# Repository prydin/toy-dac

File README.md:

# toy-dac

A 1-bit ΔΣ stereo audio DAC implemented on a Xilinx 7-series FPGA
(Digilent Cmod S7), driven from an I²S input.

The signal chain is entirely homemade RTL:

- **I²S receiver** with double-flopped synchronizers and AXI-Stream output
- **Automatic input rate detection** (32 / 44.1 / 48 kHz)
- **Fractional-phase polyphase ASRC** — 256 phases × 64 taps × 18-bit
  coefficients with 16-bit alpha lerp, single time-shared MAC, PI servo
  on the input ring-buffer fill — resampling onto a fixed
  Fs<sub>out</sub> = MCLK / 64 = 1.6875 MHz output grid
- **2nd-order CIFB ΔΣ modulator** (per channel) with TPDF dither,
  driving a single-bit differential output pin pair on each channel
- A small reconstruction filter and analog output stage on the carrier PCB

Internal test sources (silent, DC, 1 kHz DDS sine) and a bypass mode
(raw I²S → modulator) are included for bring-up and characterisation.

Achieved performance with the current build is roughly 70 dB SNR and
−74 dB THD at −7 dBFS, 1 kHz; harmonic distortion is dominated by the
analog stage on the prototype board.

## Status

**Experimental.** This is a personal learning / hobby project. The
design works end-to-end on the target hardware, but it has had limited
testing, no formal verification, and the analog board is a hand-routed
prototype. Module ports, parameter names, and pinouts may change without
notice. Use it for inspiration or as a starting point, not as a drop-in
IP.

## Repository layout

```
fpga/toy-dac/   Vivado project (RTL under src/rtl, constraints under
                toy-dac.srcs/constrs_1, simulation under toy-dac.srcs/sim_1)
kicad/dac/      KiCad schematic + PCB for the analog carrier board
scripts/        Coefficient generation, simulation helpers, sanity checks
docs/           Block diagrams (top-level + ASRC internals)
```

## Building

Open `fpga/toy-dac/toy-dac.xpr` in Vivado 2024.2, run synthesis +
implementation + bitstream generation, and program the Cmod S7. The
target part and pin assignments live in
`fpga/toy-dac/toy-dac.srcs/constrs_1/new/root.xdc`.

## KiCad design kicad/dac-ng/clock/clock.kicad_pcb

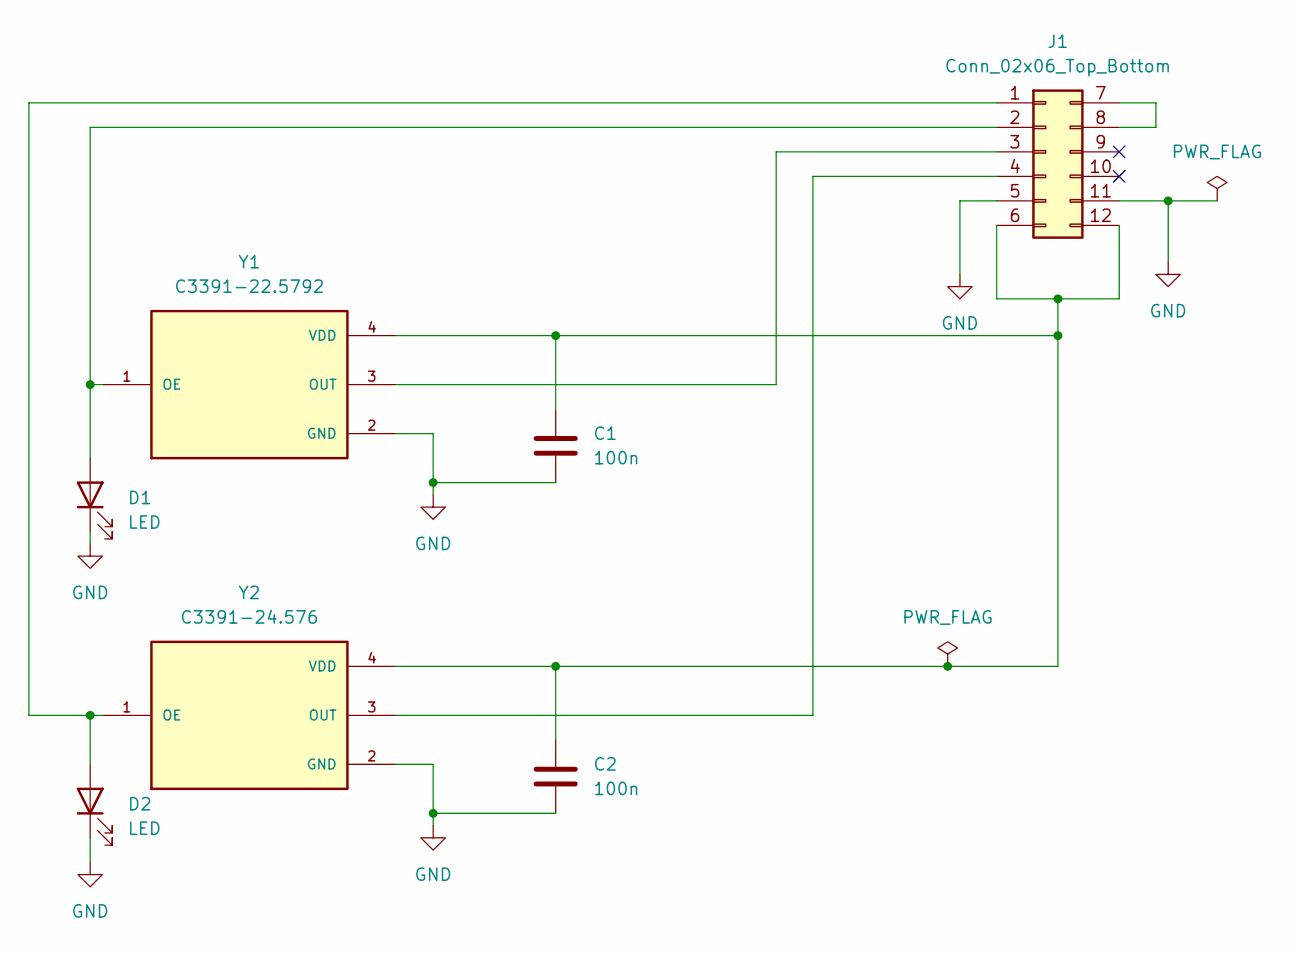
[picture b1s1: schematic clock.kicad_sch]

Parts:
C1, C2: 100n; C_0603_1608Metric_Pad1.08x0.95mm_HandSolder
D1, D2: LED; LED_0603_1608Metric
J1: Conn_02x06_Top_Bottom; PinHeader_2x06_P2.54mm_Vertical
Y1: C3391-22.5792; Oscillator_SMD_Diodes_FN-4Pin_7.0x5.0mm; PARTREV NA
Y2: C3391-24.576; Oscillator_SMD_Diodes_FN-4Pin_7.0x5.0mm; PARTREV NA

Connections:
GND: C1.2, C2.2, D1.1 (K), D2.1 (K), J1.5, J1.11, Y1.2 (GND), Y2.2 (GND)
unnamed: D1.2 (A), J1.2, Y1.1 (OE)
unnamed: D2.2 (A), J1.1, Y2.1 (OE)
unnamed: J1.3, Y1.3 (OUT)
unnamed: J1.4, Y2.3 (OUT)
unnamed: J1.7, J1.8
unnamed: C1.1, C2.1, J1.6, J1.12, Y1.4 (VDD), Y2.4 (VDD)

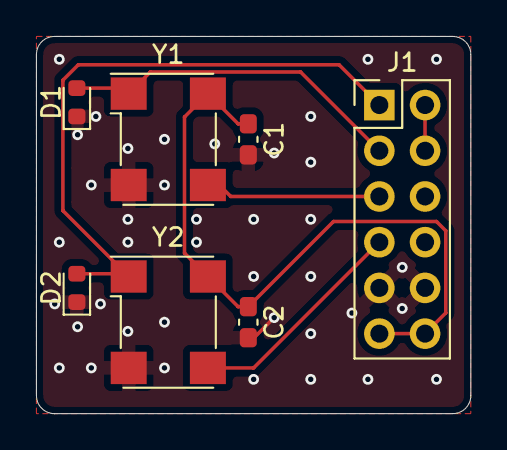
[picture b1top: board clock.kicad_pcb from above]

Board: 2 copper layers, 24.1 x 21.0 mm, 7 parts (0 on the bottom side), 7 nets.

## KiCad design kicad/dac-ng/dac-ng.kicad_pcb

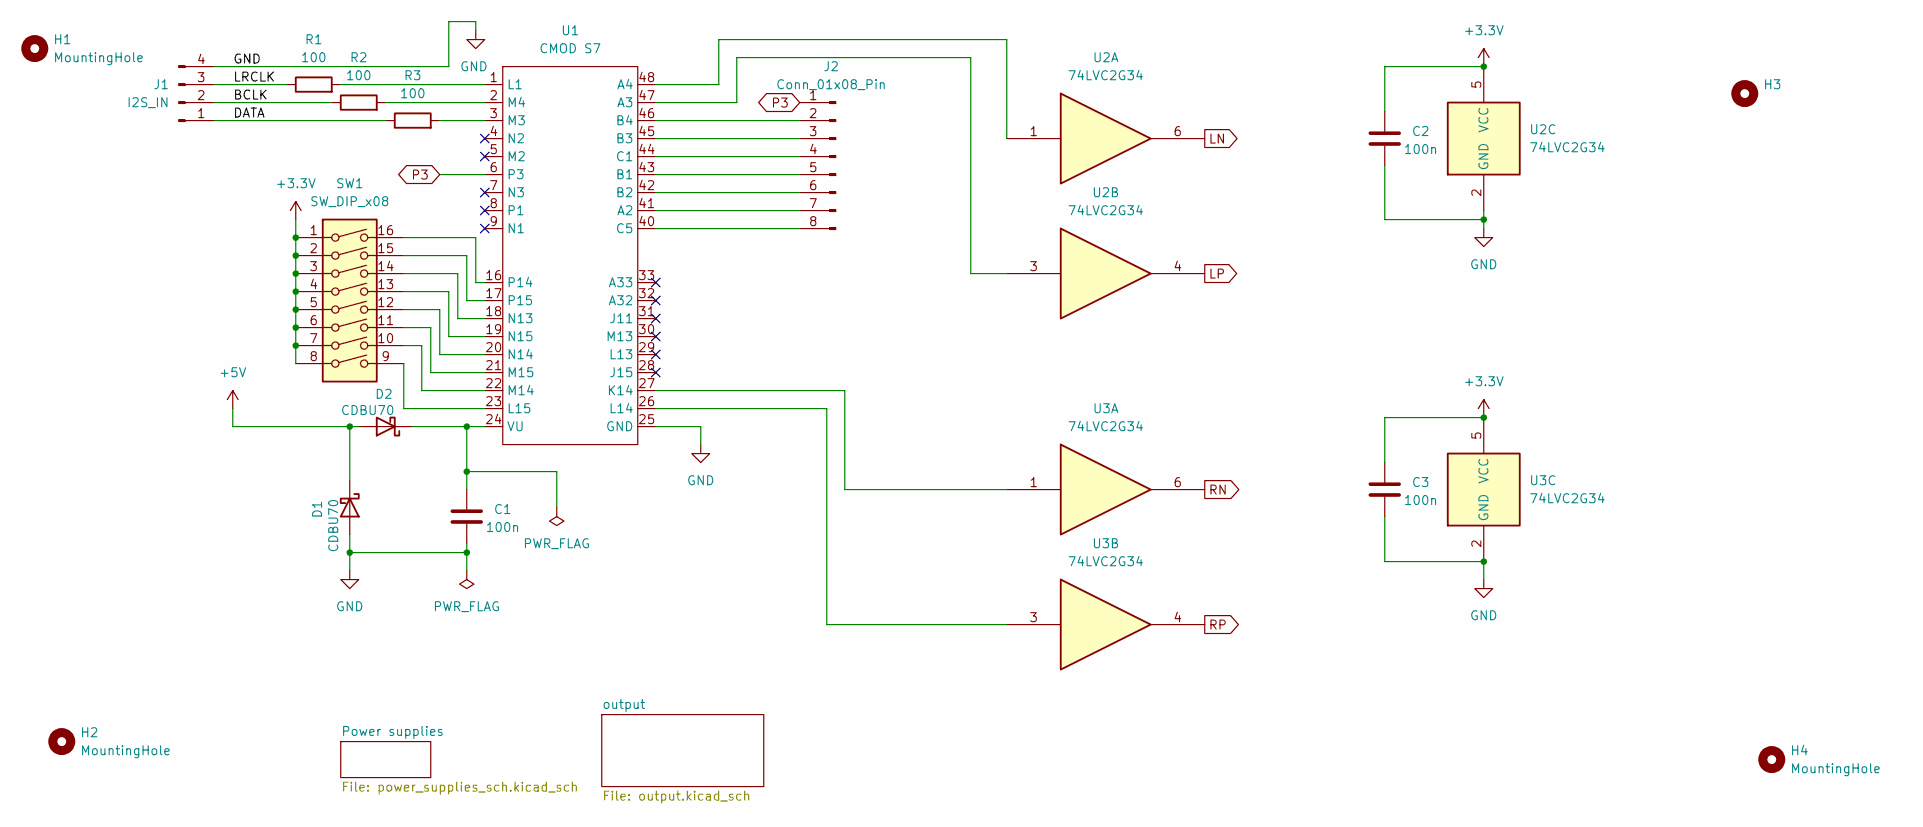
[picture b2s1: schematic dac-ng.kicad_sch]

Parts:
C1, C2, C3: 100n; C_0603_1608Metric_Pad1.08x0.95mm_HandSolder
D1, D2: CDBU70; D_0603_1608Metric
H1, H2, H3, H4: MountingHole; MountingHole_3.2mm_M3
J1: I2S_IN; JST_PH_B4B-PH-K_1x04_P2.00mm_Vertical
J2: Conn_01x08_Pin; PinHeader_1x08_P2.54mm_Vertical
R1, R2, R3: 100; R_0603_1608Metric_Pad0.98x0.95mm_HandSolder
SW1: SW_DIP_x08; SW_DIP_SPSTx08_Slide_6.7x21.88mm_W7.62mm_P2.54mm_LowProfile
U1: CMOD S7
U2, U3: 74LVC2G34; SOT-363_SC-70-6

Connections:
+3.3V: C2.2, C3.2, SW1.1, SW1.2, SW1.3, SW1.4, SW1.5, SW1.6, SW1.7, SW1.8, U2.5 (VCC), U3.5 (VCC); also elsewhere on the board
+5V: D1.1 (K), D2.2 (A); also elsewhere on the board
/BCLK: J1.2, R2.1
/DATA: J1.1, R3.1
/LRCLK: J1.3, R1.1
GND: C1.1, C2.1, C3.1, D1.2 (A), J1.4, U1.25 (GND), U2.2 (GND), U3.2 (GND); also elsewhere on the board
LN: U2.6; also elsewhere on the board
LP: U2.4; also elsewhere on the board
unnamed: C1.2, D2.1 (K), U1.24 (VU)
unnamed: J2.2, U1.46 (B4)
unnamed: J2.3, U1.45 (B3)
unnamed: J2.4, U1.44 (C1)
unnamed: J2.5, U1.43 (B1)
unnamed: J2.6, U1.42 (B2)
unnamed: J2.7, U1.41 (A2)
unnamed: J2.8, U1.40 (C5)
unnamed: U1.47 (A3), U2.3
unnamed: U1.48 (A4), U2.1
unnamed: U1.27 (K14), U3.1
unnamed: R1.2, U1.1 (L1)
unnamed: U1.26 (L14), U3.3
unnamed: SW1.9, U1.23 (L15)
unnamed: R3.2, U1.3 (M3)
unnamed: R2.2, U1.2 (M4)
unnamed: SW1.10, U1.22 (M14)
unnamed: SW1.11, U1.21 (M15)
unnamed: SW1.14, U1.18 (N13)
unnamed: SW1.12, U1.20 (N14)
unnamed: SW1.13, U1.19 (N15)
unnamed: SW1.16, U1.16 (P14)
unnamed: SW1.15, U1.17 (P15)
P3: J2.1, U1.6 (P3)
RN: U3.6; also elsewhere on the board
RP: U3.4; also elsewhere on the board

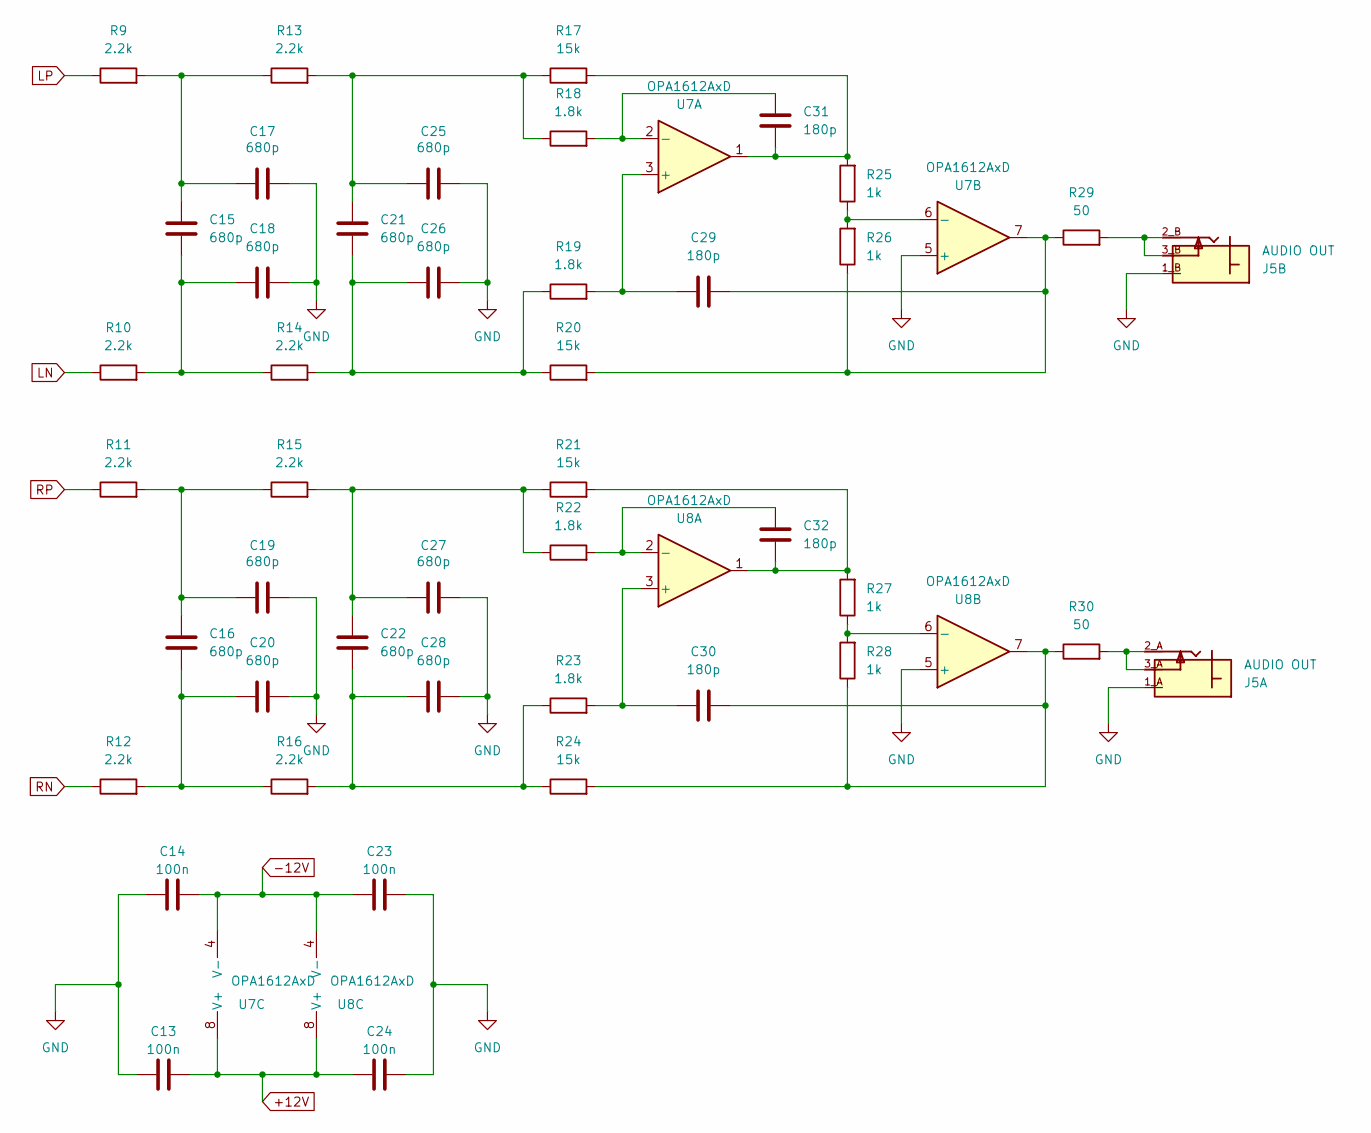
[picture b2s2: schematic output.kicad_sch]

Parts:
C13, C14, C23, C24: 100n; C_0603_1608Metric_Pad1.08x0.95mm_HandSolder
C15, C16, C17, C18, C19, C20, C21, C22, C25, C26, C27, C28: 680p; C_0603_1608Metric_Pad1.08x0.95mm_HandSolder
C29, C30, C31, C32: 180p; C_0603_1608Metric_Pad1.08x0.95mm_HandSolder
J5: AUDIO OUT; SWITCHCRAFT_PJRAN2X1U01AUX
R9, R10, R11, R12, R13, R14, R15, R16: 2.2k; R_0603_1608Metric_Pad0.98x0.95mm_HandSolder
R17, R20, R21, R24: 15k; R_0603_1608Metric_Pad0.98x0.95mm_HandSolder
R18, R19, R22, R23: 1.8k; R_0603_1608Metric_Pad0.98x0.95mm_HandSolder
R25, R26, R27, R28: 1k; R_0603_1608Metric_Pad0.98x0.95mm_HandSolder
R29, R30: 50; R_0603_1608Metric_Pad0.98x0.95mm_HandSolder
U7, U8: OPA1612AxD; SOIC-8_5.3x5.3mm_P1.27mm

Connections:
+12V: C13.2, C24.2, U7.8 (V+), U8.8 (V+); also elsewhere on the board
-12V: C14.2, C23.2, U7.4 (V-), U8.4 (V-); also elsewhere on the board
GND: C13.1, C14.1, C17.2, C18.2, C19.2, C20.2, C23.1, C24.1, C25.2, C26.2, C27.2, C28.2, J5.1_A, J5.1_B, U7.5 (+), U8.5 (+); also elsewhere on the board
LN: R10.1; also elsewhere on the board
LP: R9.1; also elsewhere on the board
unnamed: C15.1, C17.1, R9.2, R13.1
unnamed: C15.2, C18.1, R10.2, R14.1
unnamed: C16.1, C19.1, R11.2, R15.1
unnamed: C16.2, C20.1, R12.2, R16.1
unnamed: C21.1, C25.1, R13.2, R17.1, R18.1
unnamed: C21.2, C26.1, R14.2, R19.1, R20.1
unnamed: C22.1, C27.1, R15.2, R21.1, R22.1
unnamed: C22.2, C28.1, R16.2, R23.1, R24.1
unnamed: C29.2, R20.2, R26.1, R29.1, U7.7
unnamed: C30.2, R24.2, R28.1, R30.1, U8.7
unnamed: C31.2, R17.2, R25.2, U7.1
unnamed: C32.2, R21.2, R27.2, U8.1
unnamed: J5.2_A, J5.3_A, R30.2
unnamed: J5.2_B, J5.3_B, R29.2
unnamed: C29.1, R19.2, U7.3 (+)
unnamed: C31.1, R18.2, U7.2 (-)
unnamed: R25.1, R26.2, U7.6 (-)
unnamed: C30.1, R23.2, U8.3 (+)
unnamed: C32.1, R22.2, U8.2 (-)
unnamed: R27.1, R28.2, U8.6 (-)
RN: R12.1; also elsewhere on the board
RP: R11.1; also elsewhere on the board

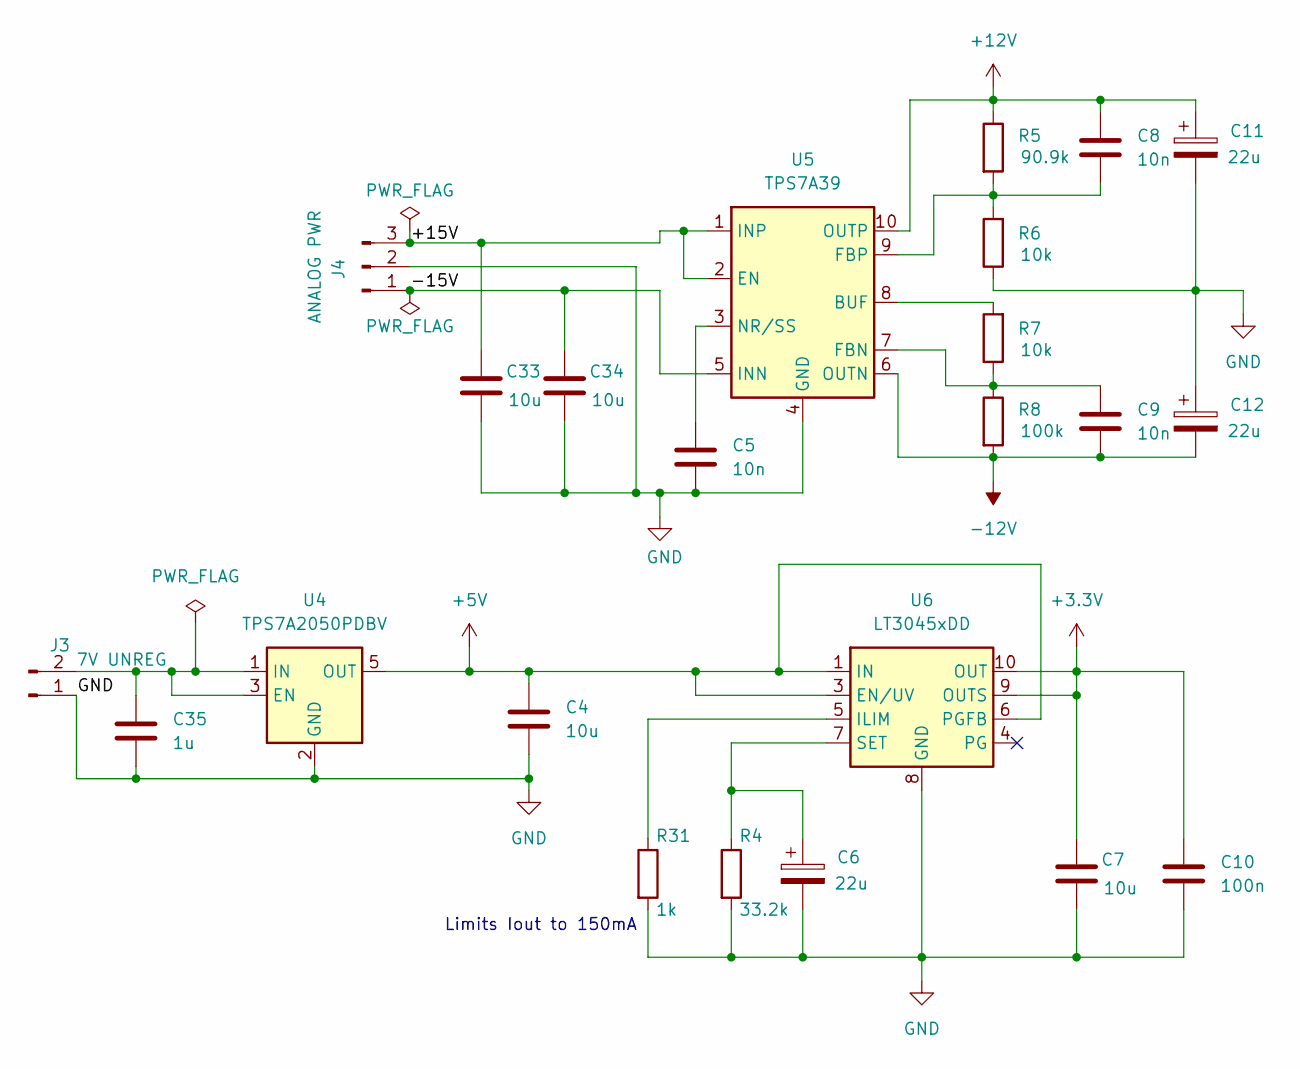
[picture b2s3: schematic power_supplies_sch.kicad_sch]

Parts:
C4, C7, C33, C34: 10u; C_0805_2012Metric
C5, C8, C9: 10n; C_0603_1608Metric_Pad1.08x0.95mm_HandSolder
C6, C11, C12: 22u; CP_EIA-3216-10_Kemet-I_HandSolder
C10: 100n; C_0603_1608Metric_Pad1.08x0.95mm_HandSolder
C35: 1u; C_0603_1608Metric
J3: 7V UNREG; JST_PH_B2B-PH-K_1x02_P2.00mm_Vertical
J4: ANALOG PWR; JST_PH_B3B-PH-K_1x03_P2.00mm_Vertical
R4: 33.2k; R_0603_1608Metric_Pad0.98x0.95mm_HandSolder
R5: 90.9k; R_0603_1608Metric_Pad0.98x0.95mm_HandSolder
R6, R7: 10k; R_0603_1608Metric_Pad0.98x0.95mm_HandSolder
R8: 100k; R_0603_1608Metric_Pad0.98x0.95mm_HandSolder
R31: 1k; R_0603_1608Metric_Pad0.98x0.95mm_HandSolder
U4: TPS7A2050PDBV; SOT-23-5
U5: TPS7A39; Texas_S-PVSON-N10_ThermalVias
U6: LT3045xDD; DFN-10-1EP_3x3mm_P0.5mm_EP1.65x2.38mm

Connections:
+3.3V: C7.1, C10.1, U6.9 (OUTS), U6.10 (OUT); also elsewhere on the board
+5V: C4.1, U4.5 (OUT), U6.1 (IN), U6.2 (IN), U6.3 (EN/UV), U6.6 (PGFB); also elsewhere on the board
+12V: C8.1, C11.1, R5.1, U5.10 (OUTP); also elsewhere on the board
-12V: C9.2, C12.2, R8.2, U5.6 (OUTN); also elsewhere on the board
/Power supplies/+15V: C33.1, J4.3, U5.1 (INP), U5.2 (EN)
/Power supplies/-15V: C34.1, J4.1, U5.5 (INN)
GND: C4.2, C5.2, C6.2, C7.2, C10.2, C11.2, C12.1, C33.2, C34.2, C35.2, J3.1, J4.2, R4.2, R6.1, R31.2, U4.2 (GND), U5.4 (GND), U5.11 (GND), U6.8 (GND), U6.11 (GND); also elsewhere on the board
unnamed: C35.1, J3.2, U4.1 (IN), U4.3 (EN)
unnamed: R7.2, U5.8 (BUF)
unnamed: C9.1, R7.1, R8.1, U5.7 (FBN)
unnamed: C8.2, R5.2, R6.2, U5.9 (FBP)
unnamed: C5.1, U5.3 (NR/SS)
unnamed: R31.1, U6.5 (ILIM)
unnamed: C6.1, R4.1, U6.7 (SET)

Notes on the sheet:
Limits Iout to 150mA

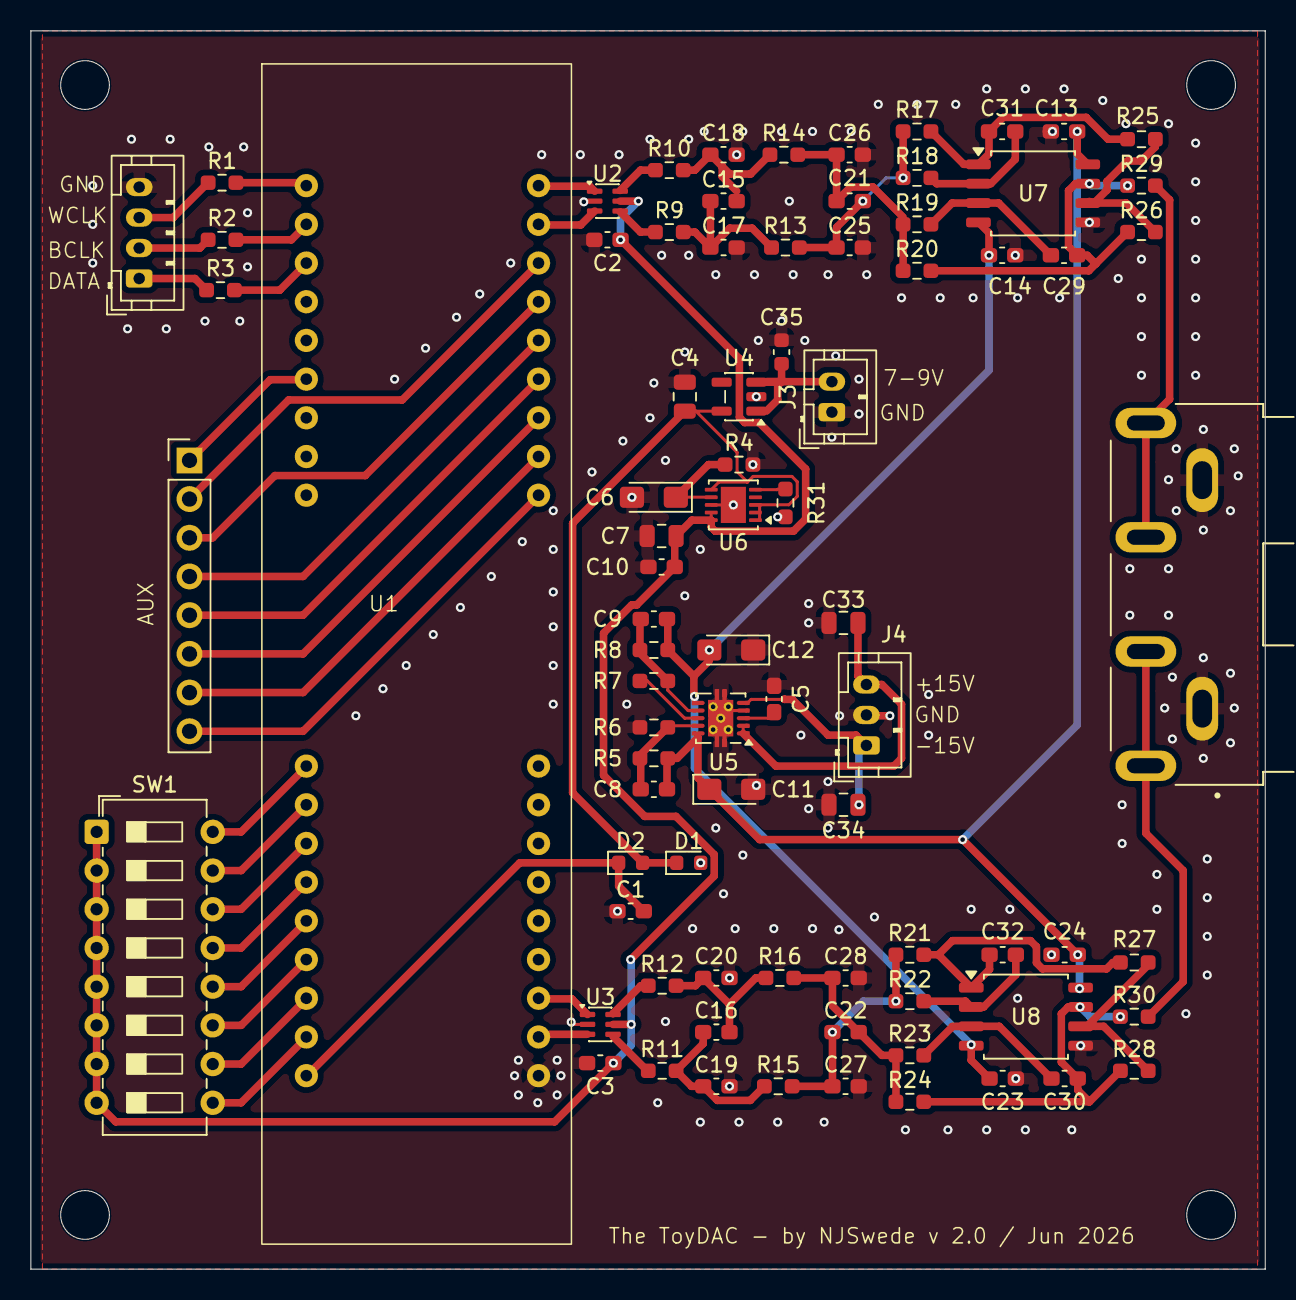
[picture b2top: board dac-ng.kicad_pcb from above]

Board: 4 copper layers, 81.0 x 81.3 mm, 86 parts (0 on the bottom side), 65 nets.

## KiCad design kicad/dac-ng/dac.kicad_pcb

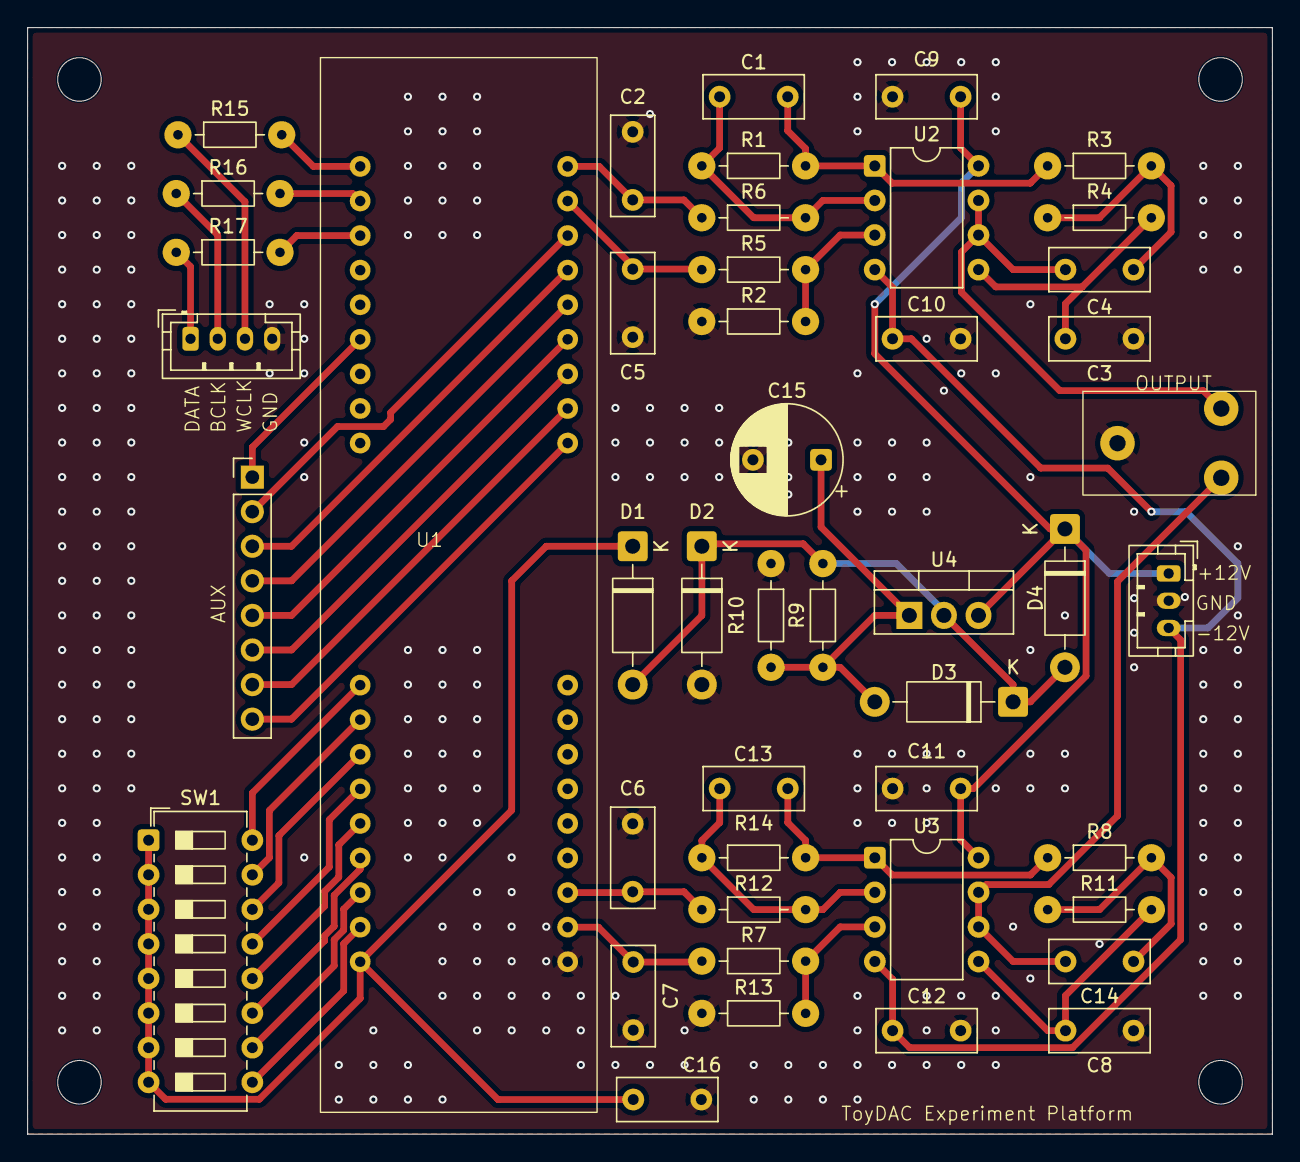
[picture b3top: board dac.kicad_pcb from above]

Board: 4 copper layers, 91.4 x 81.3 mm, 50 parts (0 on the bottom side), 44 nets.

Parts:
C1, C3, C4, C8, C13, C14: 47p; C_Rect_L7.2mm_W3.0mm_P5.00mm_FKS2_FKP2_MKS2_MKP2_HandSolder
C2, C5, C6, C7: 100p; C_Rect_L7.2mm_W3.0mm_P5.00mm_FKS2_FKP2_MKS2_MKP2_HandSolder
C9, C10, C11, C12, C16: 100n; C_Rect_L7.2mm_W3.0mm_P5.00mm_FKS2_FKP2_MKS2_MKP2_HandSolder
C15: 10u; CP_Radial_D8.0mm_P5.00mm
D1: SB140; D_DO-41_SOD81_P10.16mm_Horizontal
D2, D3, D4: 1N4004; D_DO-41_SOD81_P10.16mm_Horizontal
H1, H2, H3, H4: MountingHole; MountingHole_3.2mm_M3
J1: OUTPUT; Basic RCA
J2: Conn_01x03_Pin; JST_PH_B3B-PH-K_1x03_P2.00mm_Vertical
J3: Conn_01x08_Pin; PinHeader_1x08_P2.54mm_Vertical
J4: I2S_IN; JST_PH_B4B-PH-K_1x04_P2.00mm_Vertical
R1, R2, R13, R14: 10k; R_Axial_DIN0204_L3.6mm_D1.6mm_P7.62mm_Horizontal_HandSolder
R3, R4, R8, R11: 6.8k; R_Axial_DIN0204_L3.6mm_D1.6mm_P7.62mm_Horizontal_HandSolder
R5, R6, R7, R12: 4.7k; R_Axial_DIN0204_L3.6mm_D1.6mm_P7.62mm_Horizontal_HandSolder
R9, R10: 220; R_Axial_DIN0204_L3.6mm_D1.6mm_P7.62mm_Horizontal_HandSolder
R15, R16, R17: 100; R_Axial_DIN0204_L3.6mm_D1.6mm_P7.62mm_Horizontal_HandSolder
SW1: SW_DIP_x08; SW_DIP_SPSTx08_Slide_6.7x21.88mm_W7.62mm_P2.54mm_LowProfile
U1: CMOD S7
U2, U3: NE5532; DIP-8_W7.62mm
U4: LM317_TO-220; TO-220-3_Vertical

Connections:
+12V: C9.2, C11.2, D4.1 (K), J2.1, U2.8 (V+), U3.8 (V+), U4.3 (VI)
-12V: C10.2, C12.2, J2.3, U2.4 (V-), U3.4 (V-)
/BCLK: J4.2, R16.1
/DATA: J4.1, R17.1
/LRCLK: J4.3, R15.1
GND: C2.2, C3.2, C5.2, C6.2, C7.2, C8.2, C9.1, C10.1, C11.1, C12.1, C15.2, C16.1, D2.2 (A), J1.3 (EXT), J2.2, J4.4, R2.1, R10.1, R13.1, U1.25 (GND)
LN: C2.1, R6.1, U1.48 (A4)
LOUT: C4.2, J1.2 (IN2), U2.6 (-), U2.7
LP: C5.1, R5.1, U1.47 (A3)
unnamed: C1.1, R1.2, R3.1, U2.1
unnamed: C4.1, R3.2, R4.1
unnamed: C13.1, R8.1, R14.2, U3.1
unnamed: C14.1, R8.2, R11.1
unnamed: D1.2 (A), D2.1 (K), D3.1 (K), D4.2 (A), R9.2, U4.2 (VO)
unnamed: C16.2, D1.1 (K), SW1.1, SW1.2, SW1.3, SW1.4, SW1.5, SW1.6, SW1.7, SW1.8, U1.24 (VU)
unnamed: C15.1, D3.2 (A), R9.1, R10.2, U4.1 (ADJ)
unnamed: J3.2, U1.46 (B4)
unnamed: J3.3, U1.45 (B3)
unnamed: J3.4, U1.44 (C1)
unnamed: J3.5, U1.43 (B1)
unnamed: J3.6, U1.42 (B2)
unnamed: J3.7, U1.41 (A2)
unnamed: J3.8, U1.40 (C5)
unnamed: R15.2, U1.1 (L1)
unnamed: SW1.9, U1.23 (L15)
unnamed: R17.2, U1.3 (M3)
unnamed: R16.2, U1.2 (M4)
unnamed: SW1.10, U1.22 (M14)
unnamed: SW1.11, U1.21 (M15)
unnamed: SW1.14, U1.18 (N13)
unnamed: SW1.12, U1.20 (N14)
unnamed: SW1.13, U1.19 (N15)
unnamed: SW1.16, U1.16 (P14)
unnamed: SW1.15, U1.17 (P15)
unnamed: R2.2, R5.2, U2.3 (+)
unnamed: C1.2, R1.1, R6.2, U2.2 (-)
unnamed: C3.1, R4.2, U2.5 (+)
unnamed: R7.2, R13.2, U3.3 (+)
unnamed: C13.2, R12.2, R14.1, U3.2 (-)
unnamed: C8.1, R11.2, U3.5 (+)
P3: J3.1, U1.6 (P3)
RN: C6.1, R12.1, U1.27 (K14)
ROUT: C14.2, J1.1 (IN1), U3.6 (-), U3.7
RP: C7.1, R7.1, U1.26 (L14)

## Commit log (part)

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2026-04-12 Initial checkin
2026-04-24 Added PCB
2026-04-24 Added rate detection.
2026-04-25 Before simplification
2026-04-25 Simplified ASRC.
2026-04-27 Initial plan
2026-04-27 feat: add multirate (44.1/48 kHz) and bypass support to ASRC
    - nco.v: add inc_nominal_in port for runtime NCO frequency override
    - asrc.v: add inc_nominal_in port, pass through to internal NCO
    - root.v:
    * add bypass input port (already pinned in XDC)
    * wire lrclk_pos_edge from i2s instance
    * instantiate rate_detect to measure LRCLK period
2026-04-27 style: address code review feedback in root.v
    - Remove 4 empty unused i2s port connections (keep only lrclk_pos_edge)
    - Add comment explaining dvalid=1'b1 for rate_detect
    - Add comment clarifying window_period is unused
    Agent-Logs-Url: https://github.com/prydin/toy-dac/sessions/9c2d046f-109c-470d-b2cf-774b6617e7b4
2026-04-29 Removed generated files
2026-04-29 Removed junk files
2026-05-01 Making sound!
2026-05-02 Increased internal sample rate
2026-05-03 Moved files
2026-05-03 Cleanup
2026-05-07 Fixed adjust LED blink
